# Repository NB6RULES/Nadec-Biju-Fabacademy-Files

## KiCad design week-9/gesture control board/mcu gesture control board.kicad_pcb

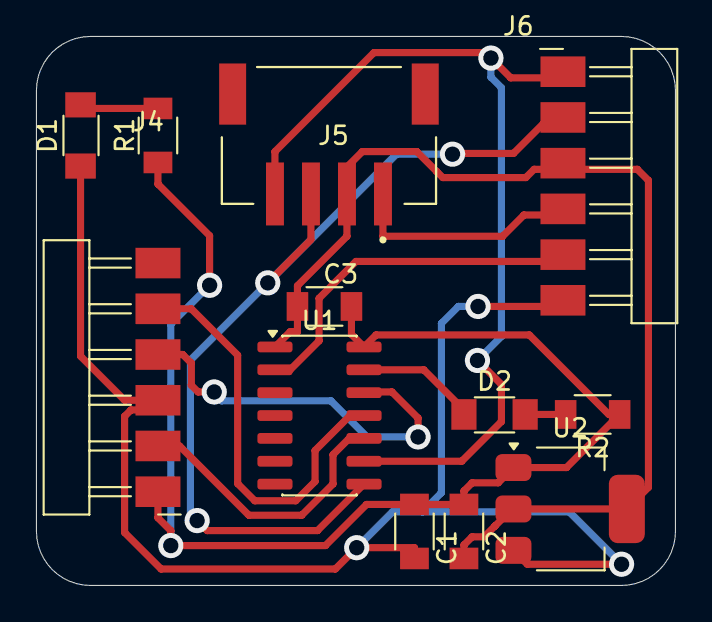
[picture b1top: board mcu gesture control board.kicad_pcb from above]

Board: 2 copper layers, 35.5 x 30.5 mm, 12 parts (0 on the bottom side), 13 nets.

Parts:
C1, C2: 10uF; C_1206
C3: 100nF; C_1206
D1, D2: LED_1206
J4: Conn_PinHeader_FTDI_1x06_P2.54mm_Horizontal_SMD; PinHeader_01x06_P2.54mm_Horizontal_SMD
J5: I2C JST; JST_S4B-PH-SM4-TB
J6: PinHeader_01x06_P2.54mm_Horizontal_SMD
R1, R2: R_1206
U1: ATtiny1624-SS; SOIC-14_3.9x8.7mm_P1.27mm
U2: AMS1117; SOT-223-3_TabPin2

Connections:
3.3v LOGIC OUT: J6.5, U1.2 (PA4)
5V IN: C1.2, D1.1 (K), J4.3, J6.6, U2.3 (VI)
DEBUG LED: D2.1 (K), U1.13 (PA3)
GND: J5.1, J6.4
unnamed: D1.2 (A), R1.2
unnamed: D2.2 (A), R2.2
PWR_GND: C1.1, C2.1, C3.2, J4.1, R1.1, R2.1, U1.14 (GND), U2.1 (ADJ)
RX: J4.4, U1.12 (PA2)
SCL: J5.4, J6.1, U1.9 (PB0)
SDA: J5.3, J6.2, U1.8 (PB1)
TX: J4.5, U1.11 (PA1)
UPDI: J4.2, U1.10 (~RESET/PA0)
VCC: C2.2, C3.1, J5.2, J6.3, U1.1 (VCC), U2.2 (VO)

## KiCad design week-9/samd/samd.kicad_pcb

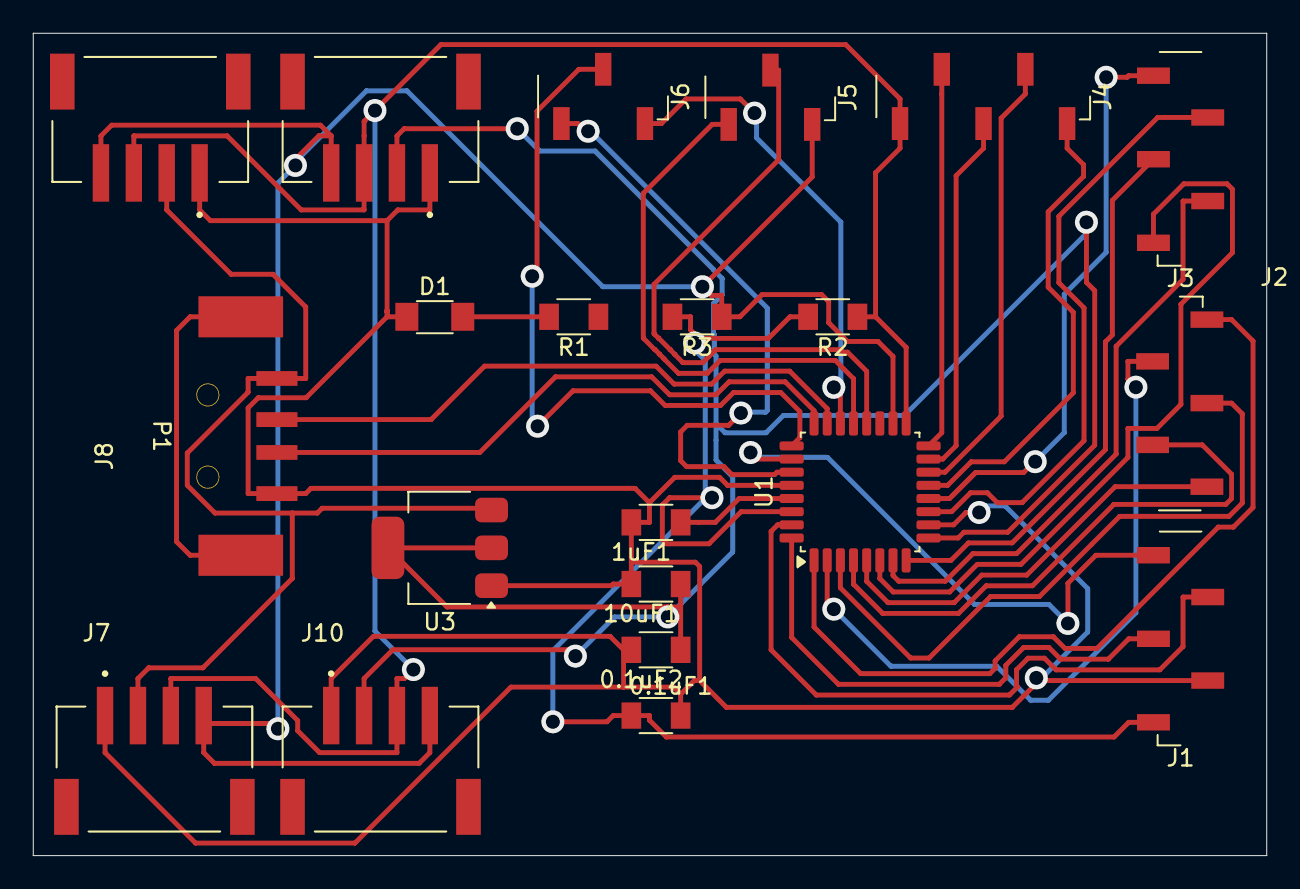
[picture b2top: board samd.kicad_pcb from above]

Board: 2 copper layers, 75.0 x 50.0 mm, 21 parts (0 on the bottom side), 32 nets.

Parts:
0.1uF1, 0.1uF2, 1uF1, 10uF1: C_1206
D1: LED_1206
J1, J2, J3, J4: PinSocket_01x05_P2.54mm_Vertical_SMD
J5, J6: PinSocket_01x03_P2.54mm_Vertical_SMD
J7, J8, J9, J10: S4B-PH-SM4-TB; JST_S4B-PH-SM4-TB
P1: Conn_USB_A_Socket_AdamTech_USB-A-S-RA-TSMT
R1: R_1206
R2, R3: 4.7K; R_1206
U1: ATSAMD21E17A-A; TQFP-32_7x7mm_P0.8mm
U3: AMS1117; SOT-223-3_TabPin2

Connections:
D+: P1.3 (D+), U1.24 (PA25)
D-: P1.2 (D-), U1.23 (PA24)
unnamed: D1.2 (A), R1.2
PA00: J2.1, U1.1 (PA00)
PA01: J2.2, U1.2 (PA01)
PA02: J2.3 (Pin_1), U1.3 (PA02)
PA03: J2.4 (Pin_2), U1.4 (PA03)
PA04: J2.5 (Pin_1), U1.5 (PA04)
PA05: J3.1, U1.6 (PA05)
PA06: J3.2, U1.7 (PA06)
PA07: J3.3 (Pin_1), U1.8 (PA07)
PA08: J3.4 (Pin_2), U1.11 (PA08)
PA09: J3.5 (Pin_1), U1.12 (PA09)
PA10: J4.1, U1.13 (PA10)
PA11: J4.2, U1.14 (PA11)
PA14: J4.3 (Pin_1), U1.15 (PA14)
PA15: J4.4 (Pin_2), U1.16 (PA15)
PA16: J4.5 (Pin_1), J7.3, J8.3, J9.3, J10.3, R2.1, U1.17 (PA16)
PA17: J5.1, J7.4, J8.4, J9.4, J10.4, R3.1, U1.18 (PA17)
PA19: J5.2, U1.20 (PA19)
PA22: J5.3 (Pin_1), U1.21 (PA22)
PA23: J6.1, U1.22 (PA23)
PA27: J6.2, U1.25 (PA27)
PA28: J6.3 (Pin_1), U1.27 (PA28)
PWR_GND: 0.1uF1.2, 0.1uF2.2, 1uF1.2, 10uF1.2, D1.1 (K), J1.2, J7.1, J8.1, J9.1, J10.1, P1.4 (GND), U1.10 (GND), U1.28 (GND), U3.1 (ADJ)
RST: J1.5 (Pin_1), U1.26 (~RESET)
SWCLK: J1.4 (Pin_2), U1.31 (PA30)
SWDIO: J1.3 (Pin_1), U1.32 (PA31)
V BUS: J7.2, J8.2, P1.1 (5V), U3.3 (VI)
VDD: 0.1uF2.1, 10uF1.1, J9.2, J10.2, U1.9 (VDDANA), U3.2 (VO)
VDD CORE: 1uF1.1, U1.29 (VDDCORE)
VDD IN: 0.1uF1.1, J1.1, R2.2, R3.2, U1.30 (VDDIN)
